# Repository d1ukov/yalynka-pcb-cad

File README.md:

# Новорічна LED-ялинка (симетричний мультивібратор)

Проєкт розроблено в межах проєктної роботи з дисципліни "Проєктна робота в СКБ «Sky»"

## Опис пристрою
Схема побудована на базі класичного симетричного мультивібратора на двох NPN-транзисторах, що забезпечує почергове миготіння двох груп світлодіодів (по 3 світлодіоди на кожній гілці ялинки). Живлення здійснюється від батареї 9V («Крона») через двоконтактний роз'єм `J1`.

## Структура репозиторію
* `/KiCad` — принципова схема (`.kicad_sch`), трасування друкованої плати (`.kicad_pcb`) та 3D-модель плати (`.step`).
* `/Fusion 360` — 3D-модель підставки з нішею під батарею живлення, пазом під плату та фінальна збірка (`.f3z`, `.step`).
* `/Images` — візуалізація всіх етапів розробки.

## Етапи розробки

### 1. Принципова електрична схема (KiCad)
Виконано розрахунок та з'єднання елементів симетричного мультивібратора, перевірено відсутність помилок (ERC).

### 2. Трасування друкованої плати (KiCad PCB)
Створено фігурний контур плати у формі ялинки (`Edge.Cuts`), виконано двошарове розведення доріжок (`F.Cu` та `B.Cu`). Перевірка DRC пройдена з результатом `0 errors`, `0 unconnected items`.

### 3. 3D-візуалізація плати (KiCad 3D Viewer)

### 4. Корпус-підставка та фінальна збірка (Fusion 360)
Спроєктовано підставку з фасками, посадковим пазом під стовбур плати, відсіком для батареї 9V та отвором для виводу дротів живлення. Виконано фінальне складання конструкції.

### 5. Симуляція роботи симетричного мультивібратора (Falstad)
Для підтвердження працездатності схеми проведено моделювання у симуляторі <a href="https://www.falstad.com/breakout/circuitjs1-analog/circuitjs.html?ctz=DwYwlgTgBAZgvAIgIwKgFwM6IAwDpsEECsqYIiAzABwBMuA7AGw1G1IAsFAnF9o+6hAAjSjVQAHEQiLZUANwiISUALaYlAUwC0SFAD4AUFCjAASlAAeiGu2xRdNKDbv9U8BLKgB3d55UBDCzlELgQAekNjYC9La1t7JEckRjsHNxxwyJMYqwRnBMcKGlTE9I9Mo2zYhCKSx1s6stkIyujqhoKodipG2AyWqOhc5Lr7FPsmJtRFZBkKwerazqWkSb7yqBn2ekJ5kyHEDocuggnGKc3DnYI94AOEbtHHs4uZpDmBkwAZAFEAEWqIzOYzsNBsZTEqgA9ogACYaGD+ACuABs0FoURpYYI3oIAOYZKDCQkqITkDz4FCfYC-AHDcZg9ggpz0SHuSEqGEIeGI1HozHYom4okEjbEjak8l4bBUrI0-6Ahms5m1CGoTlwhHItEYrE4xAoEWE8V+Mk4Sm3WntHrA56MtXQzW8nUC-XIfHGqSmqUW6lW3J2mxdG00VkOjXcrV83WCkDCkCizwm9Vmikyy0KgMh5XPVXrDlcnna-l6oUGj1ir0pn3p6k5A3jFaNxhUKZ1612Ja5lttuUgRWdltQJYUHvrJPmwjpqBgYJp6cYGaeOSww74Lj8bCsZisbBURgUEjU-tZwdUE5ni41wiG2eThdL+Srh64Gi6UdIKi0IjsIj0Cj0Lc9Y1MUwIjmOvhAe0pyrIwF7DhB-RysB4Hnpw9TJL2rTAR0o7nsUaGYeOtxoNUBFdMkzLsERkFQOIAB25ZQEIGgGjcjqRs6aDyAAQj8iBaOw+D0FwVAUNgFDbOwxRFAIUByDxADCAlULgVBEGCXDsNp-70PQVBaSR7RFBRcHPNR5zEXRjHusxrHIOxEZFnyvH8RSjBMFutAAQBHl8BQvHKRSP6-jQflgkQiRcAF7b0meVHsZBsWHDaeHBnYDRYVEwFAuhVE9FlVSnl0JnmQVxHJcg4y5qBjyFW0uRdjaZWeElcp4ostWpaBkVskhrRQlAGg2aEUAYOIiCuOsFgBXRGRZFE4jyYSGDkkgzQLSYS1zrNq2TiwtxhFCcqDcNBqQuNk1ye4M0SOWm3ANtK1rRtlSLctNSoHtaYHdSR2GMAYTgBAhhAA">Falstad Circuit Simulator</a> з реальними номіналами елементів (<code>VCC = 9 В</code>, <code>R1 = R4 = 150 Ом</code>, <code>R2 = R3 = 47 кОм</code>, <code>C1 = C2 = 10 мкФ</code>).

Під час симуляції гілки світлодіодів `D1–D3` та `D4–D6` почергово перемикаються у протифазі (коли ліва гілка відкрита та світиться, права — закрита, і навпаки). Теоретичний період повного циклу перемикання становить:

$$T \approx 0.7 \cdot (R_2 C_1 + R_3 C_2) = 0.7 \cdot (47\cdot 10^3 \cdot 10\cdot 10^{-6} + 47\cdot 10^3 \cdot 10\cdot 10^{-6}) \approx 0.66\text{ с}$$

*(Частота блимання кожної гілки — близько **1.5 Гц**).*

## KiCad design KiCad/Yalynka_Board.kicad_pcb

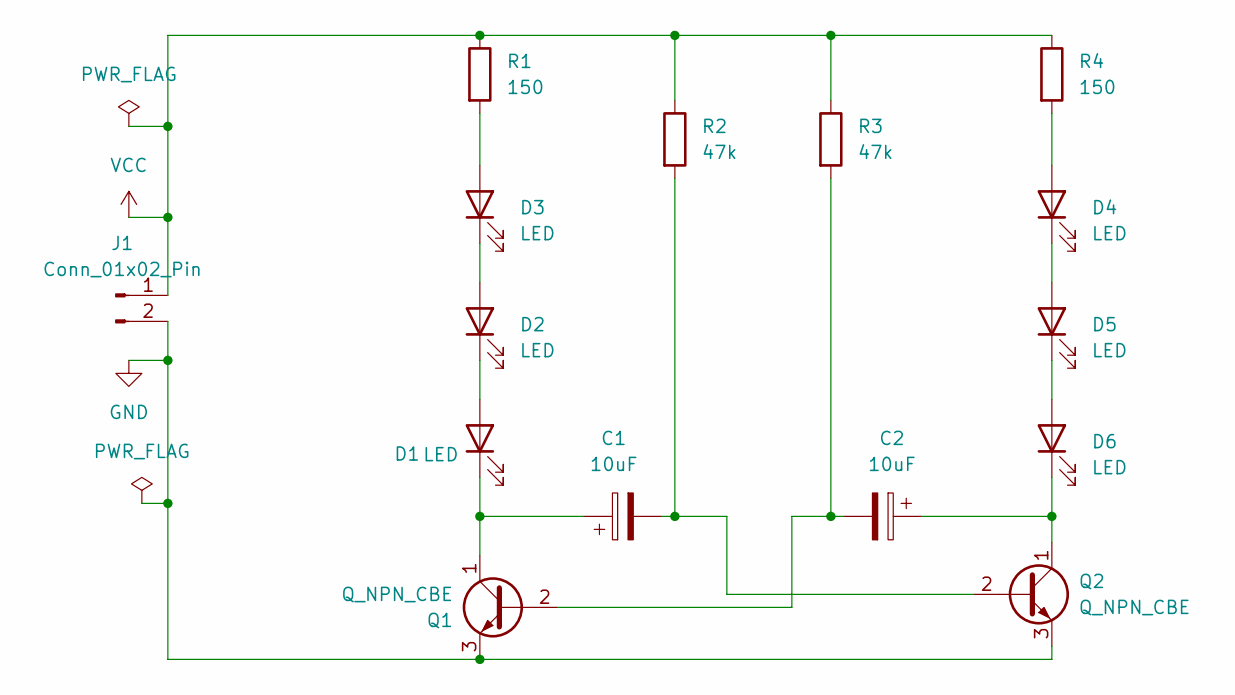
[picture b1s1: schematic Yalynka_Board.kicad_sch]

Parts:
C1, C2: 10uF; CP_Radial_D5.0mm_P2.00mm
D1, D2, D3, D4, D5, D6: LED; LED_D5.0mm
J1: Conn_01x02_Pin; PinHeader_1x02_P2.54mm_Vertical
Q1, Q2: Q_NPN_CBE; TO-92_Inline
R1, R4: 150; R_Axial_DIN0207_L6.3mm_D2.5mm_P10.16mm_Horizontal
R2, R3: 47k; R_Axial_DIN0207_L6.3mm_D2.5mm_P10.16mm_Horizontal

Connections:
GND: J1.2, Q1.3 (E), Q2.3 (E)
unnamed: D1.2 (A), D2.1 (K)
unnamed: C1.1, D1.1 (K), Q1.1 (C)
unnamed: D2.2 (A), D3.1 (K)
unnamed: D3.2 (A), R1.2
unnamed: D4.2 (A), R4.2
unnamed: D4.1 (K), D5.2 (A)
unnamed: D5.1 (K), D6.2 (A)
unnamed: C2.1, D6.1 (K), Q2.1 (C)
unnamed: C2.2, Q1.2 (B), R3.2
unnamed: C1.2, Q2.2 (B), R2.2
VCC: J1.1, R1.1, R2.1, R3.1, R4.1

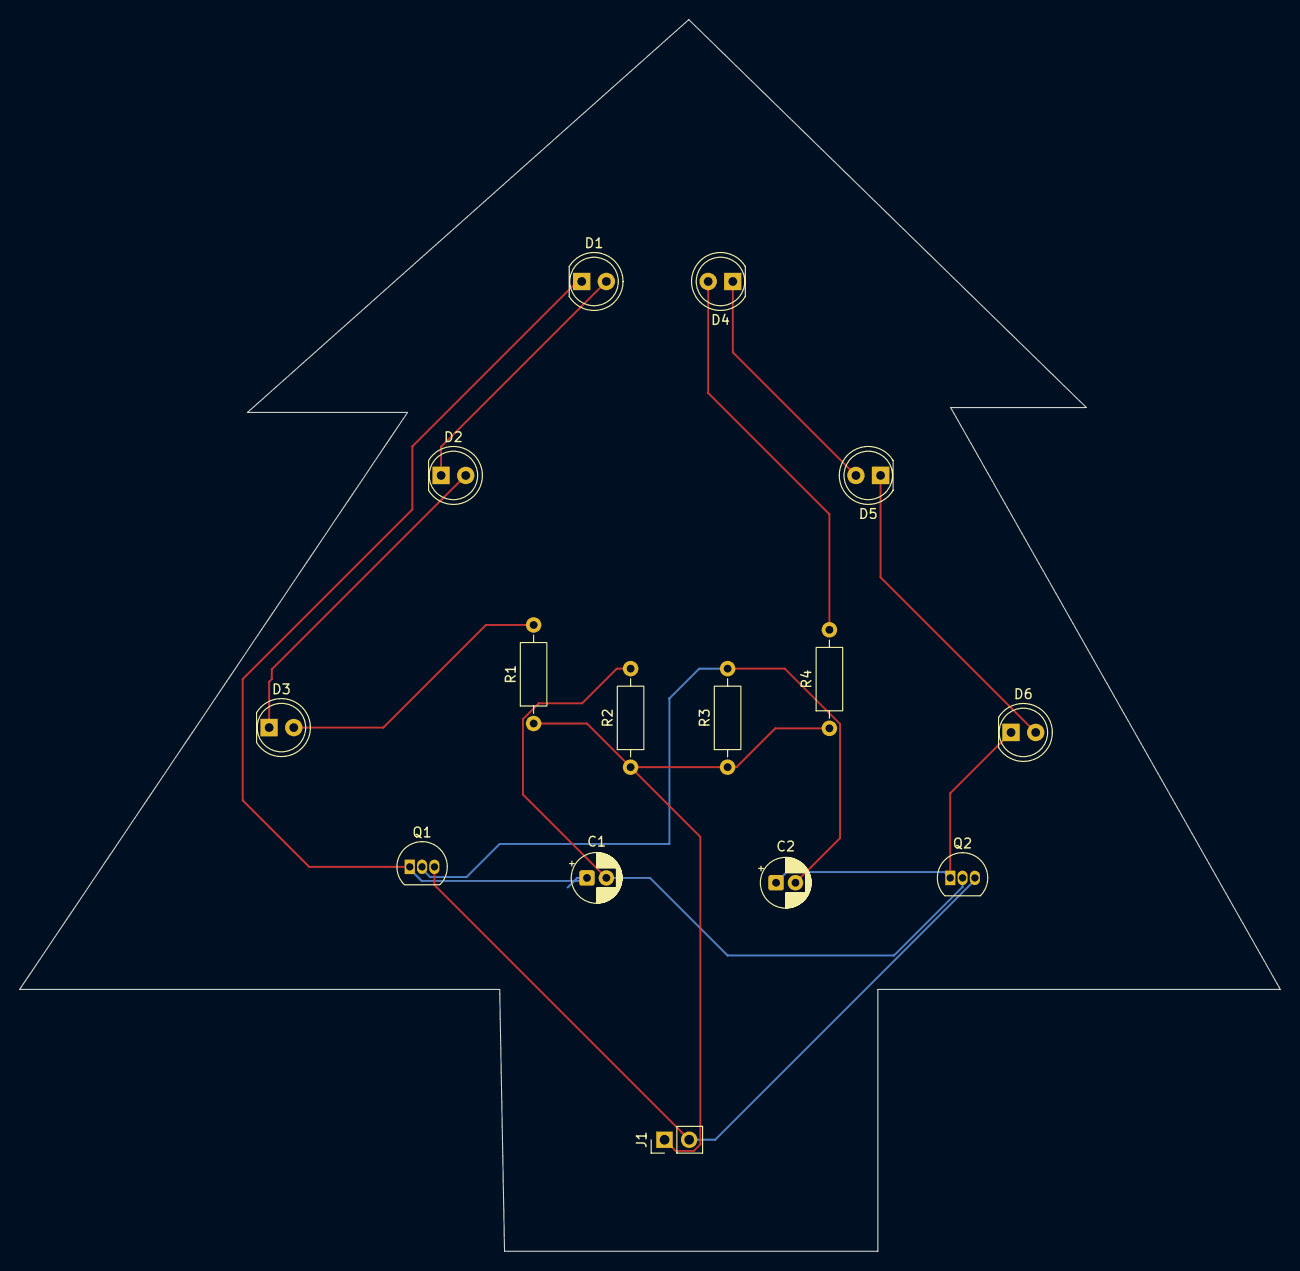
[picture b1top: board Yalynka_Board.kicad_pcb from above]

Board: 2 copper layers, 130.0 x 127.0 mm, 15 parts (0 on the bottom side), 12 nets.
